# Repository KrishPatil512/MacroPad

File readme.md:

MacroKeyboard Project

A simple custom macro keyboard built to trigger shortcuts, automate tasks, and speed up everyday workflows.

This project is a compact macro keyboard using a microcontroller (like ESP32) and programmable buttons to send custom key inputs to a computer. It can be used for productivity, gaming, or creative workflows.

 Features
Custom programmable keys
Supports keyboard shortcuts/macros
Compact and portable design
Easy to modify and expand
Can be used with different layouts

 Hardware Used
ESP32 / microcontroller
Mechanical switches / buttons
PCB 
OLED .96 in screen
Optional: enclosure (3D printed or case)
 How It Works

Each button is mapped to a specific function. When pressed, the microcontroller sends a signal to the computer (via USB) that acts like a keyboard input.

Example:

Button 1 → Copy (Ctrl + C)
Button 2 → Paste (Ctrl + V)
Button 3 → Open app
 Setup
Clone the repository
Upload code to the microcontroller
Connect via USB
Customize key mappings in code
 Project Structure
/code → firmware and logic
/pcb → PCB design files
/cad → enclosure / case design
/bom → bill of materials
 Future Improvements
Rotary encoder support
OLED display
Wireless (Bluetooth) control
Custom software interface

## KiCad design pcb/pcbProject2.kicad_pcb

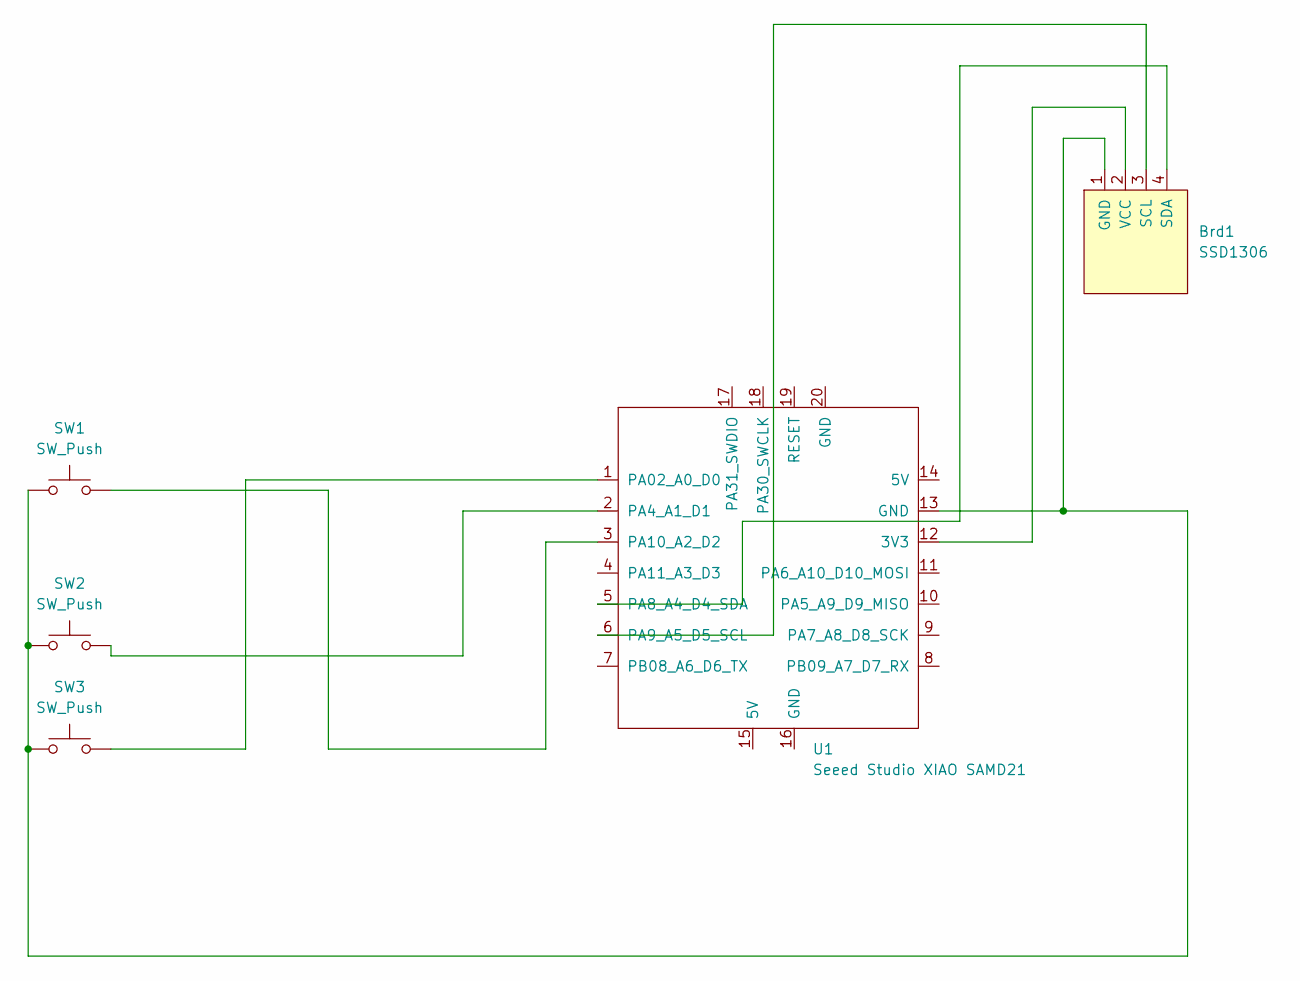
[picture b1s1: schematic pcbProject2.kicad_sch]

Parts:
Brd1: SSD1306; 128x64OLED
SW1, SW2, SW3: SW_Push; SW_Cherry_MX_1.00u_PCB
U1: Seeed Studio XIAO SAMD21; XIAO-Generic-Thruhole-14P-2.54-21X17.8MM

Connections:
unnamed: Brd1.1 (GND), SW1.1, SW2.1, SW3.1, U1.13 (GND)
unnamed: Brd1.3 (SCL), U1.6 (PA9_A5_D5_SCL)
unnamed: Brd1.4 (SDA), U1.5 (PA8_A4_D4_SDA)
unnamed: Brd1.2 (VCC), U1.12 (3V3)
unnamed: SW3.2, U1.1 (PA02_A0_D0)
unnamed: SW2.2, U1.2 (PA4_A1_D1)
unnamed: SW1.2, U1.3 (PA10_A2_D2)

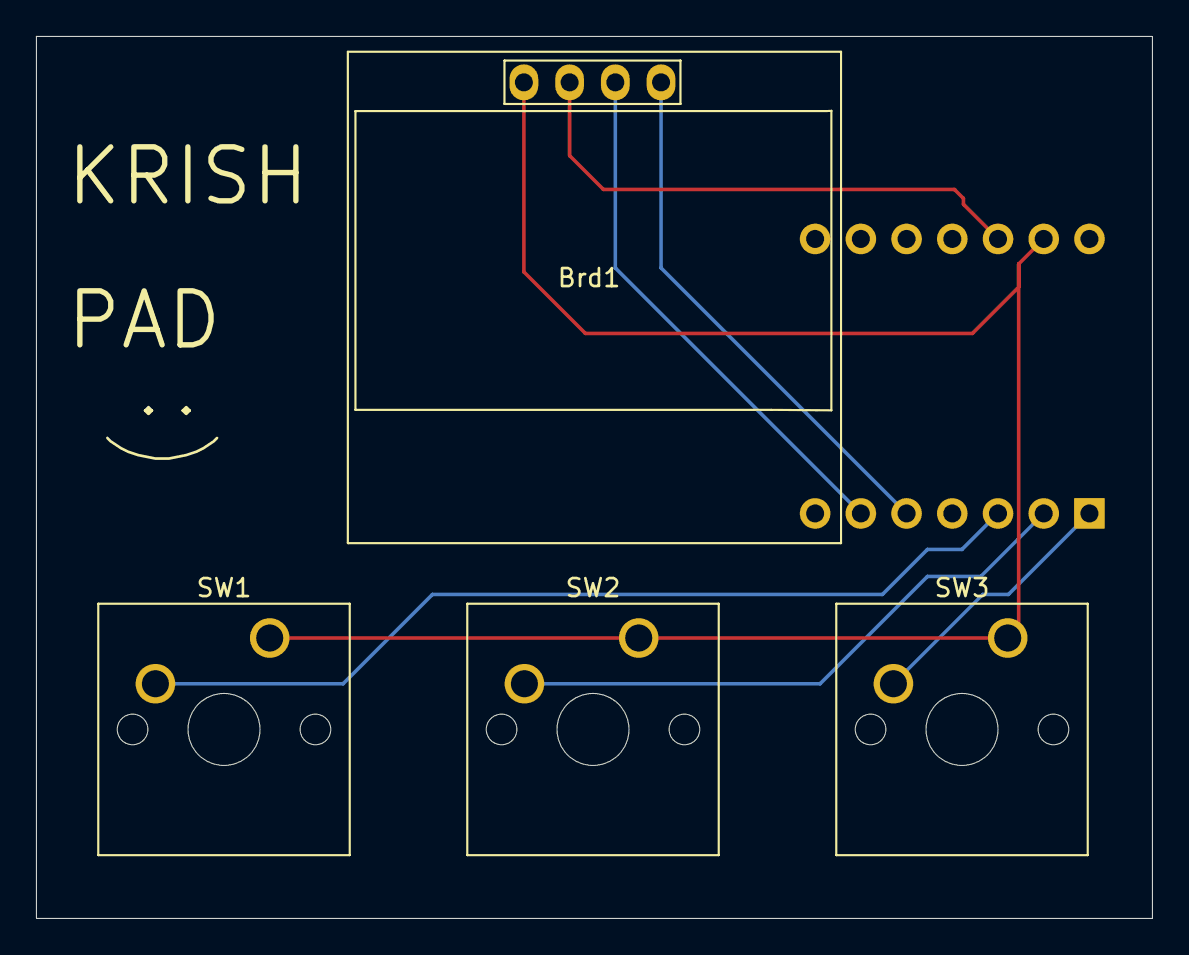
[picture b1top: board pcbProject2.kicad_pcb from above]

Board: 2 copper layers, 62.0 x 49.0 mm, 5 parts (1 on the bottom side), 7 nets.

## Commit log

2026-05-03 csv bom
2026-05-03 readme
2026-05-03 readme2
2026-05-03 added step
2026-05-04 gerbers
2026-05-13 changes to fillet etc
